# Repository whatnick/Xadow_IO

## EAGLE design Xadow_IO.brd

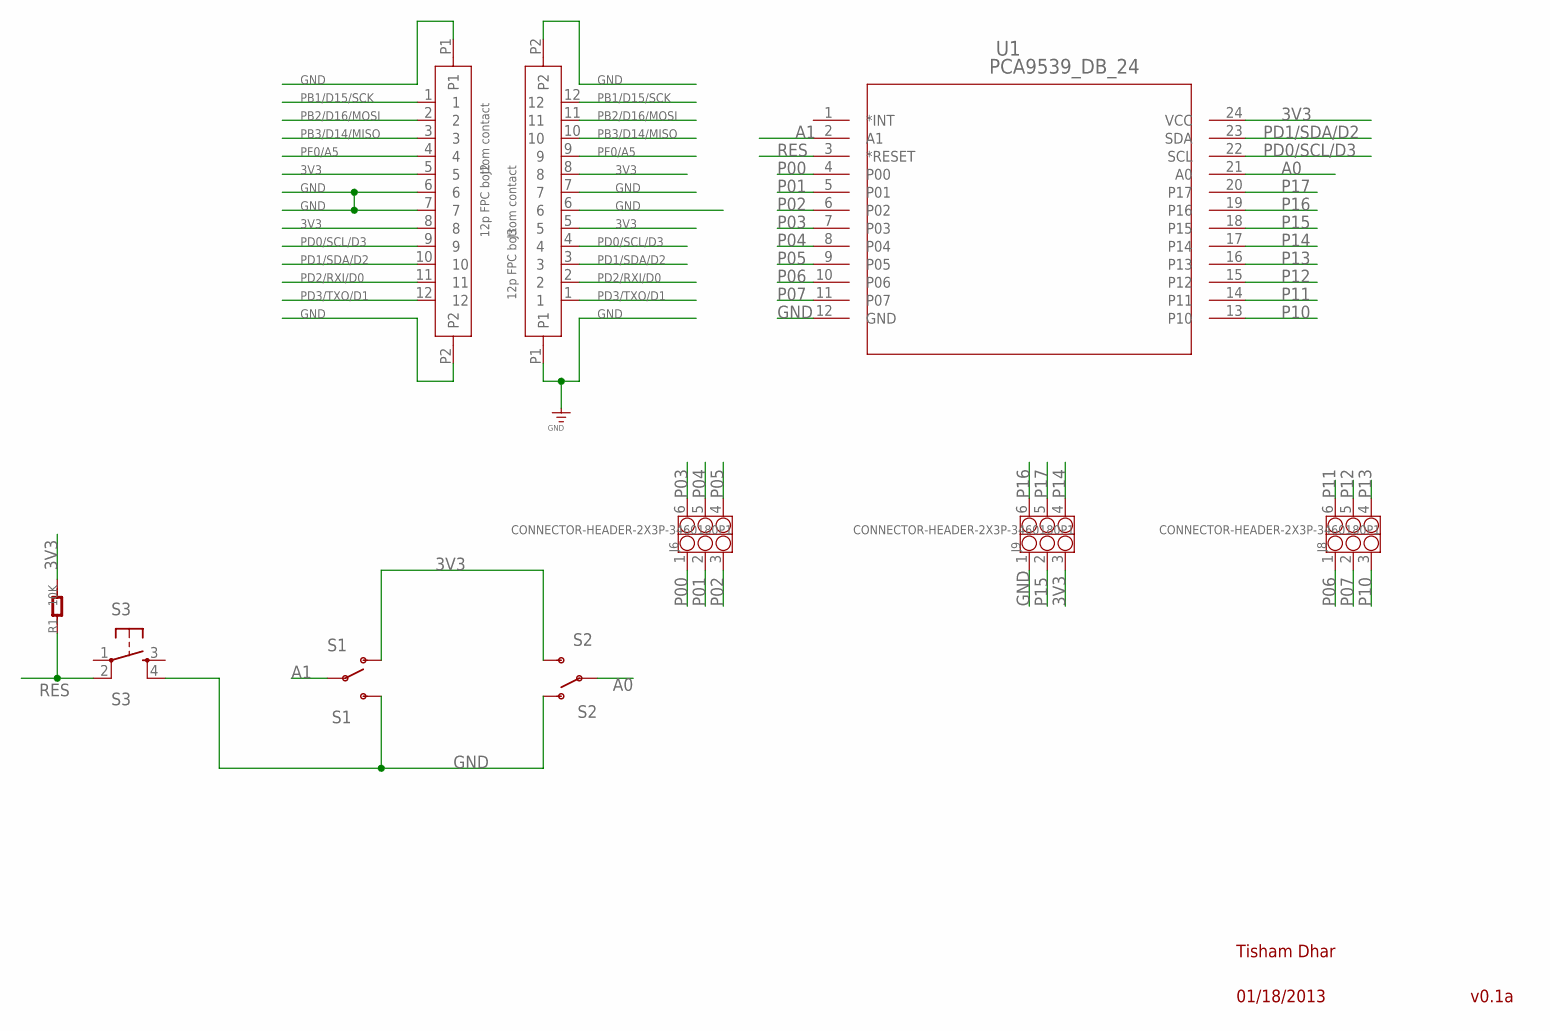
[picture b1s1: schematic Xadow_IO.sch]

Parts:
J2, J3: 12p FPC bottom contact; 12P-0.5
J6, J8, J9: CONNECTOR-HEADER-2X3P-3460180P1; 2X3P-2.54-2.54-11.6-3.0-BLACK-MALE
R1: 10K; R0603
S1: S1; SWITCH-SPST-SMD-A
S2: S2; SWITCH-SPST-SMD-A
S3: S3; TACTILE_SWITCH_SMD
U1: PCA9539_DB_24; DB24

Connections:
3V3: J2.5, J2.8, J3.5, J3.8, J9.3, R1.2, S1.1 (O), S2.3 (S), U1.24 (VCC)
A0: S2.2, U1.21 (A0)
A1: S1.2, U1.2 (A1)
GND: J2.6, J2.7, J2.P1, J2.P2, J3.6, J3.7, J3.P1, J3.P2, J9.1, S1.3 (S), S2.1 (O), S3.4, U1.12 (GND)
P00: J6.1, U1.4 (P00)
P01: J6.2, U1.5 (P01)
P02: J6.3, U1.6 (P02)
P03: J6.6, U1.7 (P03)
P04: J6.5, U1.8 (P04)
P05: J6.4, U1.9 (P05)
P06: J8.1, U1.10 (P06)
P07: J8.2, U1.11 (P07)
P10: J8.3, U1.13 (P10)
P11: J8.6, U1.14 (P11)
P12: J8.5, U1.15 (P12)
P13: J8.4, U1.16 (P13)
P14: J9.4, U1.17 (P14)
P15: J9.2, U1.18 (P15)
P16: J9.6, U1.19 (P16)
P17: J9.5, U1.20 (P17)
PB1/D15/SCK: J2.1, J3.12
PB2/D16/MOSI: J2.2, J3.11
PB3/D14/MISO: J2.3, J3.10
PD0/SCL/D3: J2.9, J3.4, U1.22 (SCL)
PD1/SDA/D2: J2.10, J3.3, U1.23 (SDA)
PD2/RXI/D0: J2.11, J3.2
PD3/TXO/D1: J2.12, J3.1
PF0/A5: J2.4, J3.9
RES: R1.1, S3.2, U1.3 (*RESET)

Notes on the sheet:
Tisham Dhar
01/18/2013
v0.1a

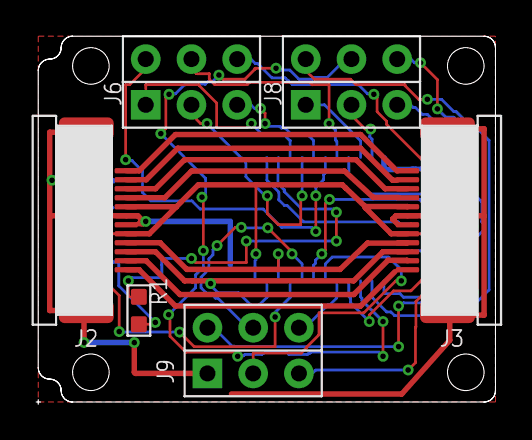
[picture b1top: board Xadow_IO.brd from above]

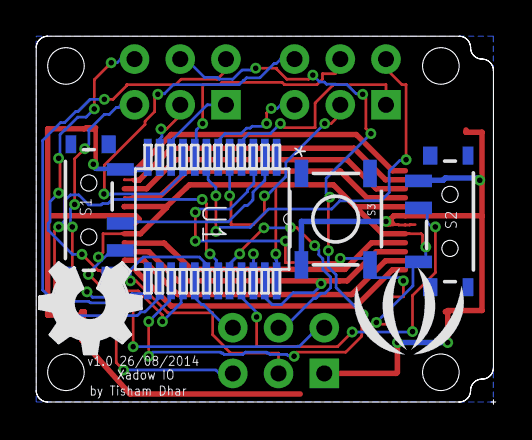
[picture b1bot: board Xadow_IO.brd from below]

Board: 2 copper layers, 25.4 x 20.3 mm, 12 parts (6 on the bottom side), 29 nets.

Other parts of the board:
U$2: LOGO_SILK
U$3: OSHW_FILLX200_NOTEXT

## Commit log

2014-09-12 Xadow Io board
2014-09-30 Changed to latest SeeedStudio DRU

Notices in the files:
parts and their libraries:
SparkFun-Electromechanical: Licensing: CC v3.0 Share-Alike You are welcome to use this library for commercial purposes.
